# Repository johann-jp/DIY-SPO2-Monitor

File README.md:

# DIY SpO₂ Monitor

A custom PCB designed in **KiCad 10** for a portable Arduino Nano-based pulse oximeter. This project uses the **MAX30102** optical sensor to measure blood oxygen saturation (SpO₂) and heart rate, displaying the readings on an **SSD1306 OLED** display.

---

## Features

- Real-time SpO₂ monitoring
- Heart rate measurement
- SSD1306 OLED display
- Menu navigation using push buttons
- Alarm LED/Buzzer indication
- Arduino Nano based
- Custom PCB designed in KiCad 10

---

## Hardware Used

- Arduino Nano
- MAX30102 Pulse Oximeter Sensor
- SSD1306 OLED Display (I2C)
- Push Buttons
- LED/Buzzer
- Resistors
- Capacitors

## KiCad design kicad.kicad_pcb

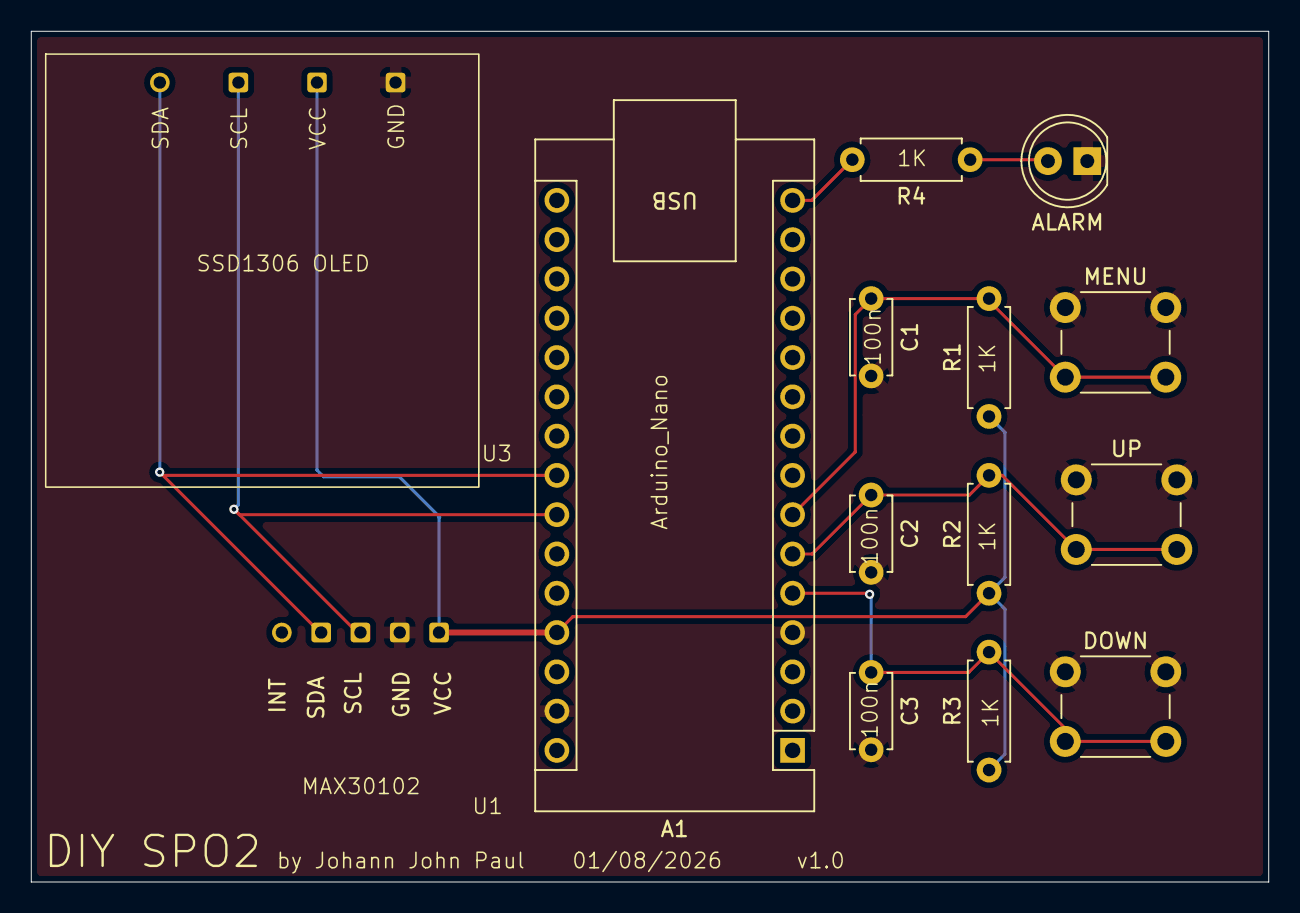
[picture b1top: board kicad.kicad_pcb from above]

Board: 4 copper layers, 80.0 x 55.0 mm, 14 parts (0 on the bottom side), 9 nets.

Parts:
A1: Arduino_Nano_v3.x; Arduino_Nano
ALARM: LED; LED_D5.0mm
C1, C2, C3: 100n; C_Disc_D4.7mm_W2.5mm_P5.00mm
DOWN: SW_Push; SW_PUSH_6mm
MENU: SW_Push; SW_PUSH_6mm
R1, R2, R3, R4: 1k; R_Axial_DIN0207_L6.3mm_D2.5mm_P7.62mm_Horizontal
U1: MAX30102; MAX30102_MODULE
U3: SSD1306
UP: SW_Push; SW_PUSH_6mm

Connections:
+5V: A1.27 (+5V), R1.1, R2.1, R3.1, U1.5 (VCC), U3.3 (VCC)
GND: A1.4 (GND), A1.29 (GND), ALARM.1 (K), C1.2, C2.2, C3.2, DOWN.1, MENU.1, U1.4 (GND), U3.4 (GND), UP.1
unnamed: A1.23 (A4), U1.2 (SDA), U3.1 (SDA)
unnamed: A1.24 (A5), U1.3 (SCL), U3.2 (SCL)
unnamed: A1.5 (D2), C3.1, DOWN.2, R3.2
unnamed: A1.6 (D3), C2.1, R2.2, UP.2
unnamed: A1.7 (D4), C1.1, MENU.2, R1.2
unnamed: A1.15 (D12), R4.2
unnamed: ALARM.2 (A), R4.1
